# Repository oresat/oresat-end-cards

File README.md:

# "End Card" PCBs for OreSat

OreSat cards in the top position (#1) and bottom position (#20) are special because they interface with
both the solar arrays and with the end caps. They also tend to hold deployable antennas.

## Features

- 4 solar panel connectors
- 3 available RF connectors
- Alternative backplane connectors only (since the solar panel connectors take up the main connector spot)

## Connector information

- TBD.

## LICENSE

Copyright Portland State Aerospace Society 2022.

This documentation describes Open Hardware and is licensed under the CERN OHL v2

You may redistribute and modify this documentation under the terms of the CERN OHL v.1.2. [https://ohwr.org/cernohl](https://ohwr.org/cernohl). This documentation is distributed WITHOUT ANY EXPRESS OR IMPLIED WARRANTY, INCLUDING OF MERCHANTABILITY, SATISFACTORY QUALITY AND FITNESS FOR A PARTICULAR PURPOSE. Please see the CERN OHL v2 for applicable conditions.

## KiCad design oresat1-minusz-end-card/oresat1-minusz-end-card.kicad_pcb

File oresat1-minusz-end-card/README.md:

---
title: "**OreSat1 -Z End Card**"
subtitle: |
  **Fabrication and Assembly Information**\
  For build TIME-STAMP
fontsize: 10pt
geometry:
  - margin=0.5in
toc: true
toc-depth: 2
colorlinks: true
urlcolor: blue
---

\newpage

# About this Board

## Board Description

The OreSat1 -Z End Card fits in the very "bottom" slot (Slot #20?) in the OreSat1 2U backplane. It's special because it hosts whatever antenna is on the -Z face of the satellite, which in this case is an L band monopole, a UHF band monopole, and an L1 band GPS patch antenna. The -Z End Card:

- Connects to the backplane with a main connector and three RF SMPM connectors
- Connects two -Z solar modules to the backplane (two of the solar module spots are taken up by the copper radiator panels for the CFC assembly)
- Routes an SMPM connector to a U.FL connector to jump up to the -Z End Cap's L1 band GPS patch antenna
- Has an OPD circuit to control:
   - Deploying the monopole antennas
   - Switching C3-UART to any of the -Z solar modules

## Documentation Links

- -Z End Card Git repository: <https://github.com/oresat/oresat-end-cards>
- **TODO:** -Z End Card Design Notes + Design Review Notes

## Documentation Files

| Filename                        | Notes                                    |
| ------------------------------- | ---------------------------------------- |
| README.pdf                      | This README file                         |
| PROJECT-NAME-outline.dxf        | Board outline (with holes) in DXF format |
| PROJECT-NAME-pcba.step          | 3D model of PCBA (with components)       |
| PROJECT-NAME-render-bot.jpg     | Render of the top of the 3D model        |
| PROJECT-NAME-render-bot.jpg     | Render of the bottom of the 3D model     |
| PROJECT-NAME-schematic.pdf      | PDF of board schematics                  |

## Contact Information

- Website: <https://www.oresat.org/>
- Email: <oresat@pdx.edu>
- Instagram: @pdxaerospace

## Board Renders

{width=50%}
{width=50%}

\newpage

# Printed Circuit Board (PCB) Fabrication Information

## Board Info

- 4 layer board
- Bounding box is 99.8 x 94.6 mm (3.93 x 3.72 in)
- Board thickness is 1.59 mm (0.063 inch)
- **Important:** See Materials and Stack Up sections below

## Board Requirements

- Design Rules
    - Minimum Trace / Space design rules
       - Outer layers: 0.127 mm (5.0 mil) / 0.127 mm (5.0 mil)
       - Inner layers: 0.127 mm (5.0 mil) / 0.127 mm (5.0 mil)
    - Outer dimension router tolerance: +/- 0.254 mm (10.0 mil)
    - Hole placement tolerance: +/- 0.075 mm (3.0 mil)
    - Inner tab routed slot tolerance: +/- 0.254 mm (10.0 mil)
- Drills
   - Drill Positional Tolerance: 0.051 mm (2.0 mil)
   - Drill Size tolerance: +/- 0.064 mm (2.5 mil)
- Plated/Un-plated holes
  - There are 16 un-plated (NPT) holes
  - There are 434 plated through (PTH) holes
  - PTH minimum diameter: 0.254 mm (10 mil)
  - PTH minimum annulus: 0.102 mm (4 mil) radius
- Outline/Routing
  - Requires a 1.0 mm or smaller diameter routing bit
- Slots
  - There are two 1.0 mm plated slots.
- Cutouts
  - There is are two cutouts.
- There are 3 fiducials on the top layer and 3 fiducials on the bottom layer.
- Panel tabs ("mouse bites")
   - Card edges must be smooth; no mouse bites or other intrusions into the card outline.
   - If external mouse bites are required, minimize and customer will remove by hand before assembly.
- If not otherwise specified, build to IPC 6012 Class 2 or better.

## Materials

- Controlled impedance
   - The stackup is critical for the performance of high speed signals on this board.
   - As long as the stackup is controlled, the board is not considered controlled impedance.
- Isola FR408HR or material with equivalent Dk.
- Board Surface treatment should be ENIG, althogh immersion Silver is acceptable.
- White silkscreen on top and bottom surface
- Taiyo PSR-4000 or equivalent soldermask on top and bottom, no requirements for color.

## Stack Up

| Layer         | Thickness           | Notes                                        |
|---------------|---------------------|----------------------------------------------|
| Top Copper    | 0.043 mm /  1.7 mil |  Layer 1 foil, 1 oz Cu after plating         |
| prepreg       | 0.200 mm /  7.9 mil |  Prepreg - Isola FR408HR 2113                |
| Layer 2       | 0.018 mm /  0.7 mil |  Layer 2 foil, 0.5 oz Cu                     |
| Core          | 0.991 mm /   39 mil |  Core Isola FR408HR                          |
| Layer 3       | 0.018 mm /  0.7 mil |  Layer 3 foil, 0.5 oz Cu                     |
| prepreg       | 0.200 mm /  7.9 mil |  Prepreg - Isola FR408HR 2113                |
| Bottom Copper | 0.043 mm /  1.7 mil |  Layer 4 foil, 1 oz copper after plating     |
| **Total Stackup** | **1.588 mm / 62.5 mil** |                                      |

## Array / Panel Information

- Coordinate with Contract Manufacturer (CM) for optimal size of this panel.
- If no feedback from CM, then produce single boards (no panel).

## Fabrication Files

### IPC-2581 File

| Filename                 | Notes                                   |
| ------------------------ | --------------------------------------- |
| PROJECT-NAME-ipc2581.xml | IPC-2581 board information file         |

### Legacy PCB Files

| Filename                      | Notes                                         |
| ------------------------------| --------------------------------------------- |
| PROJECT-NAME-Edge_Cuts.gbr    | RS274X file for the dimension (outline) layer |
| PROJECT-NAME-F_Silkscreen.gbr | RS274X file for the top silkscreen            |
| PROJECT-NAME-F_Mask.gbr       | RS274X file for the top soldermask            |
| PROJECT-NAME-F_Cu.gbr         | RS274X file for the top copper layer          |
| PROJECT-NAME-In1_Cu.gbr       | RS274X file for the layer 2 copper            |
| PROJECT-NAME-In2_Cu.gbr       | RS274X file for the layer 3 copper            |
| PROJECT-NAME-B_Cu.gbr         | RS274X file for the bottom copper layer       |
| PROJECT-NAME-B_Mask.gbr       | RS274X file for the bottom soldermask         |
| PROJECT-NAME-B_Silkscreen.gbr | RS274X file for the bottom silkscreen         |
| PROJECT-NAME-NPTH.drl         | Excellon file for non-plated through holes    |
| PROJECT-NAME-PTH.drl          | Excellon file for plated through holes        | 

\newpage

# Printed Circuit Board Assembly (PCBA) Information

## Assembly Info

- Components are on the top and bottom side of the board.
- This PCBA is mostly surface mount (SMT) with a few (THT) components.

## Assembly Requirements

- Assemble to IPC Class 2 or better
- Bake components that are not moisture sealed to appropriate levels as required.
- Solder paste MUST be leaded.
- Aqueous flux and wash strongly preferred.
   - Clean to NASA Standard "Visibly Clean (VC)": No particles or residues are visible to the naked eye.
- No conformal coating.
- Ship in antistatic protective bag

## Component Specific Assembly Information

- SMPM connectors (CM1 - CM3) should be hand-addedaccording to SOP (there is no solder paste for their footprints).
- Monopole antennas must be hand added according to the Antenna SOP.
- Resistor R1 must be hand added according to the OreSat End Card Deployment Resistor Mounting SOP.
- Press fit nuts HW1 - HW6 may be *carefully* added after SMT assembly is completed.

## Assembly Files

### IPC-2581 File

| Filename                 | Notes                           |
| ------------------------ | ------------------------------- |
| PROJECT-NAME-ipc2581.xml | IPC-2581 board information file |

### Bill of Materials (BOM)

| Filename             | Description                            |
| -------------------- | -------------------------------------- |
| PROJECT-NAME-bom.csv | BOM in Comma Separated Variable format |

### Solder Paste Stencils

| Filename                 | Notes                                            |
| ------------------------ | ------------------------------------------------ |
| PROJECT-NAME-B_Paste.gbr | RS274X file for top/front solder paste stencil   |
| PROJECT-NAME-F_Paste.gbr | RS274X file for bottom/back solder paste stencil |

### Mounting/Placement Location

| Filename            | Description                                 |
| ------------------- | ------------------------------------------- |
| PROJECT-NAME-3u.pos | Pick and place locations for components     |

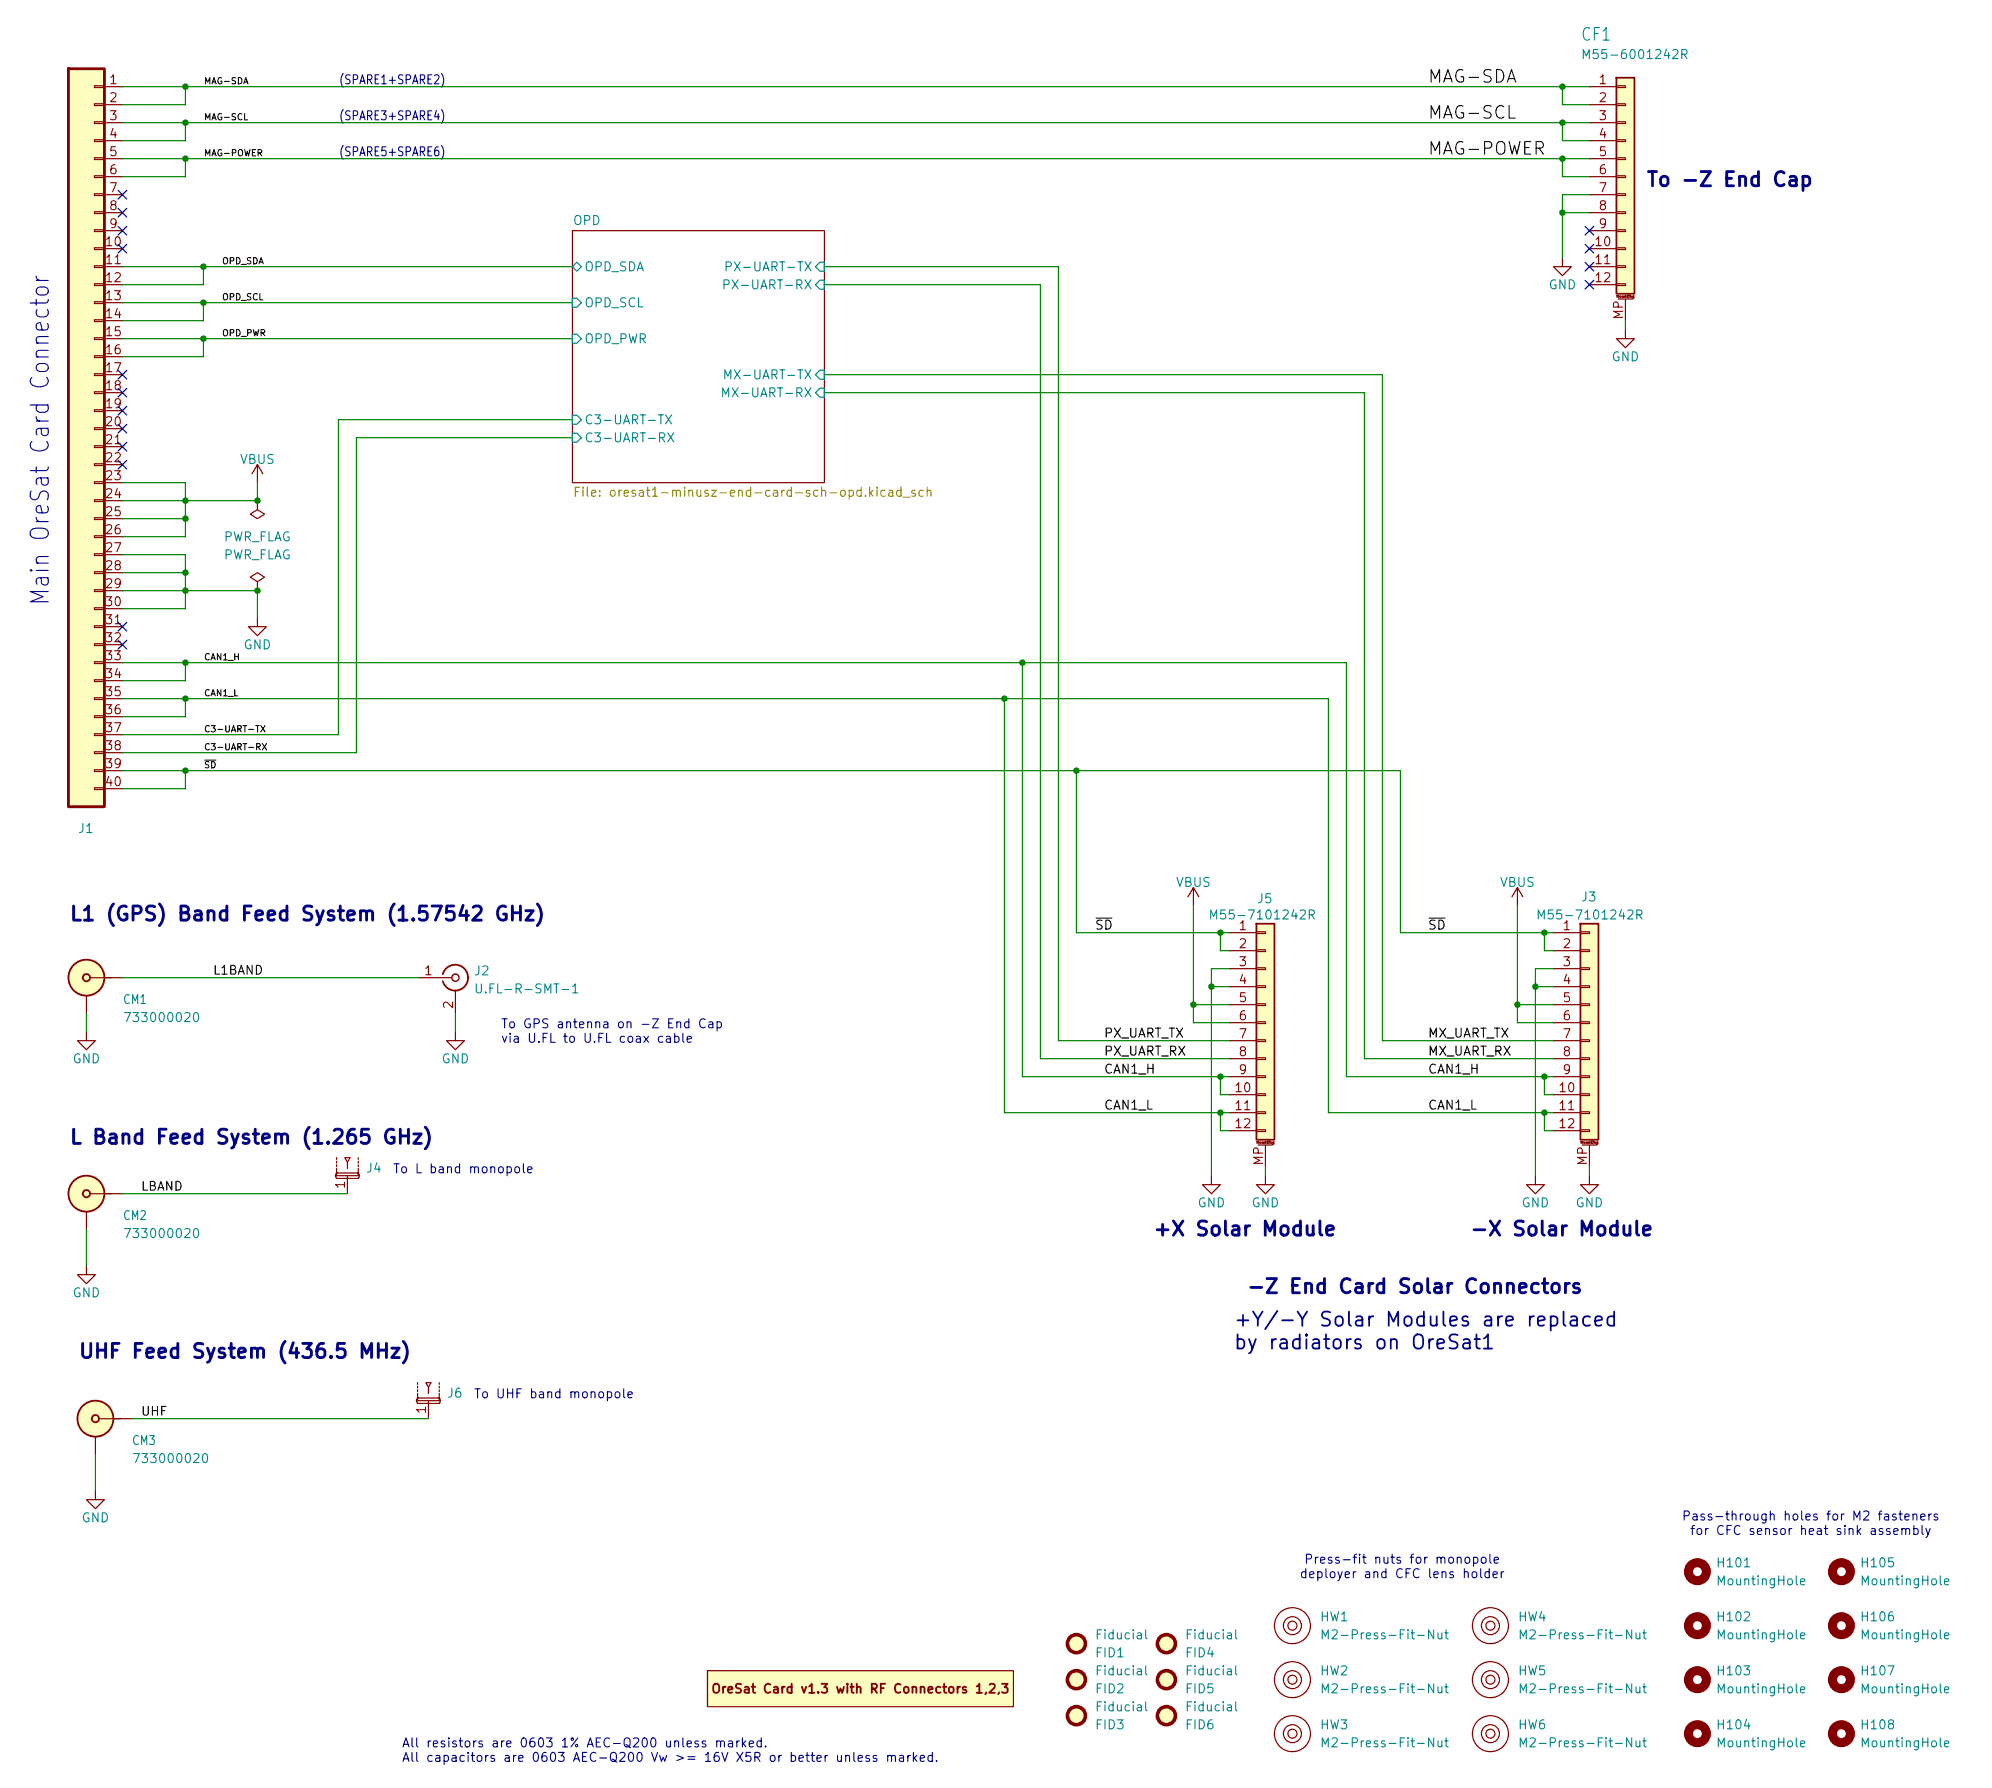
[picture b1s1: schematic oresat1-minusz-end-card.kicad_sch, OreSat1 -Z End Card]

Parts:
CF1: M55-6001242R; J-Harwin-M55-60X1242R; MPN M55-6001242R
CM1, CM2, CM3: 733000020; J-MOLEX-SMPM-073300-002X; MPN 2477330-1
FID1, FID2, FID3, FID4, FID5, FID6: Fiducial; Fiducial_1mm_Mask2mm
H101, H102, H103, H104, H105, H106, H107, H108: MountingHole; MountingHole_5mm
HW1, HW2, HW3, HW4, HW5, HW6: M2-Press-Fit-Nut; MPN N/A
J1: J-SAMTEC-TFM-120-01-L-D-RA; J-SAMTEC-TFM-120-X1-XXX-D-RA; MPN TFM-120-01-L-D-RA
J2: U.FL-R-SMT-1; U.FL_Hirose_U.FL-R-SMT-1_Vertical; MPN U.FL-R-SMT-1(10)
J3, J5: M55-7101242R; J-Harwin-M55-7101242R; MPN M55-7101242R
J4, J6: tape-measure-slot-antenna
PCB1: ORESAT-CARD-V1.3-GENERIC-3RF; ORESAT-CARD-V1.3-3RF

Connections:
/C3-UART-RX: J1.38; also elsewhere on the board
/C3-UART-TX: J1.37; also elsewhere on the board
/CAN1_H: J1.33, J1.34, J3.9, J3.10, J5.9, J5.10
/CAN1_L: J1.35, J1.36, J3.11, J3.12, J5.11, J5.12
/L1BAND: CM1.1 (SIG), J2.1 (In)
/LBAND: CM2.1 (SIG), J4.1
/MAG-POWER: CF1.5, CF1.6, J1.5, J1.6
/MAG-SCL: CF1.3, CF1.4, J1.3, J1.4
/MAG-SDA: CF1.1, CF1.2, J1.1, J1.2
/MX_UART_RX: J3.8; also elsewhere on the board
/MX_UART_TX: J3.7; also elsewhere on the board
/OPD_PWR: J1.15, J1.16; also elsewhere on the board
/OPD_SCL: J1.13, J1.14; also elsewhere on the board
/OPD_SDA: J1.11, J1.12; also elsewhere on the board
/PX_UART_RX: J5.8; also elsewhere on the board
/PX_UART_TX: J5.7; also elsewhere on the board
/UHF: CM3.1 (SIG), J6.1
/~SD: J1.39, J1.40, J3.1, J3.2, J5.1, J5.2
GND: CF1.7, CF1.8, CF1.MP (MountPin), CM1.2 (SHLD), CM2.2 (SHLD), CM3.2 (SHLD), J1.27, J1.28, J1.29, J1.30, J2.2 (Ext), J3.3, J3.4, J3.MP (MountPin), J5.3, J5.4, J5.MP (MountPin); also elsewhere on the board
VBUS: J1.23, J1.24, J1.25, J1.26, J3.5, J3.6, J5.5, J5.6; also elsewhere on the board

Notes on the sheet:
(SPARE5+SPARE6)
(SPARE3+SPARE4)
-Z End Card Solar Connectors
Pass-through holes for M2 fasteners for CFC sensor heat sink assembly
To L band monopole
+Y/-Y Solar Modules are replaced by radiators on OreSat1
All resistors are 0603 1% AEC-Q200 unless marked. All capacitors are 0603 AEC-Q200 Vw >= 16V X5R or better unless marked.
+X Solar Module
Main OreSat Card Connector
Press-fit nuts for monopole deployer and CFC lens holder
To UHF band monopole
(SPARE1+SPARE2)
UHF Feed System (436.5 MHz)
L1 (GPS) Band Feed System (1.57542 GHz)
To -Z End Cap
To GPS antenna on -Z End Cap via U.FL to U.FL coax cable
L Band Feed System (1.265 GHz)
-X Solar Module

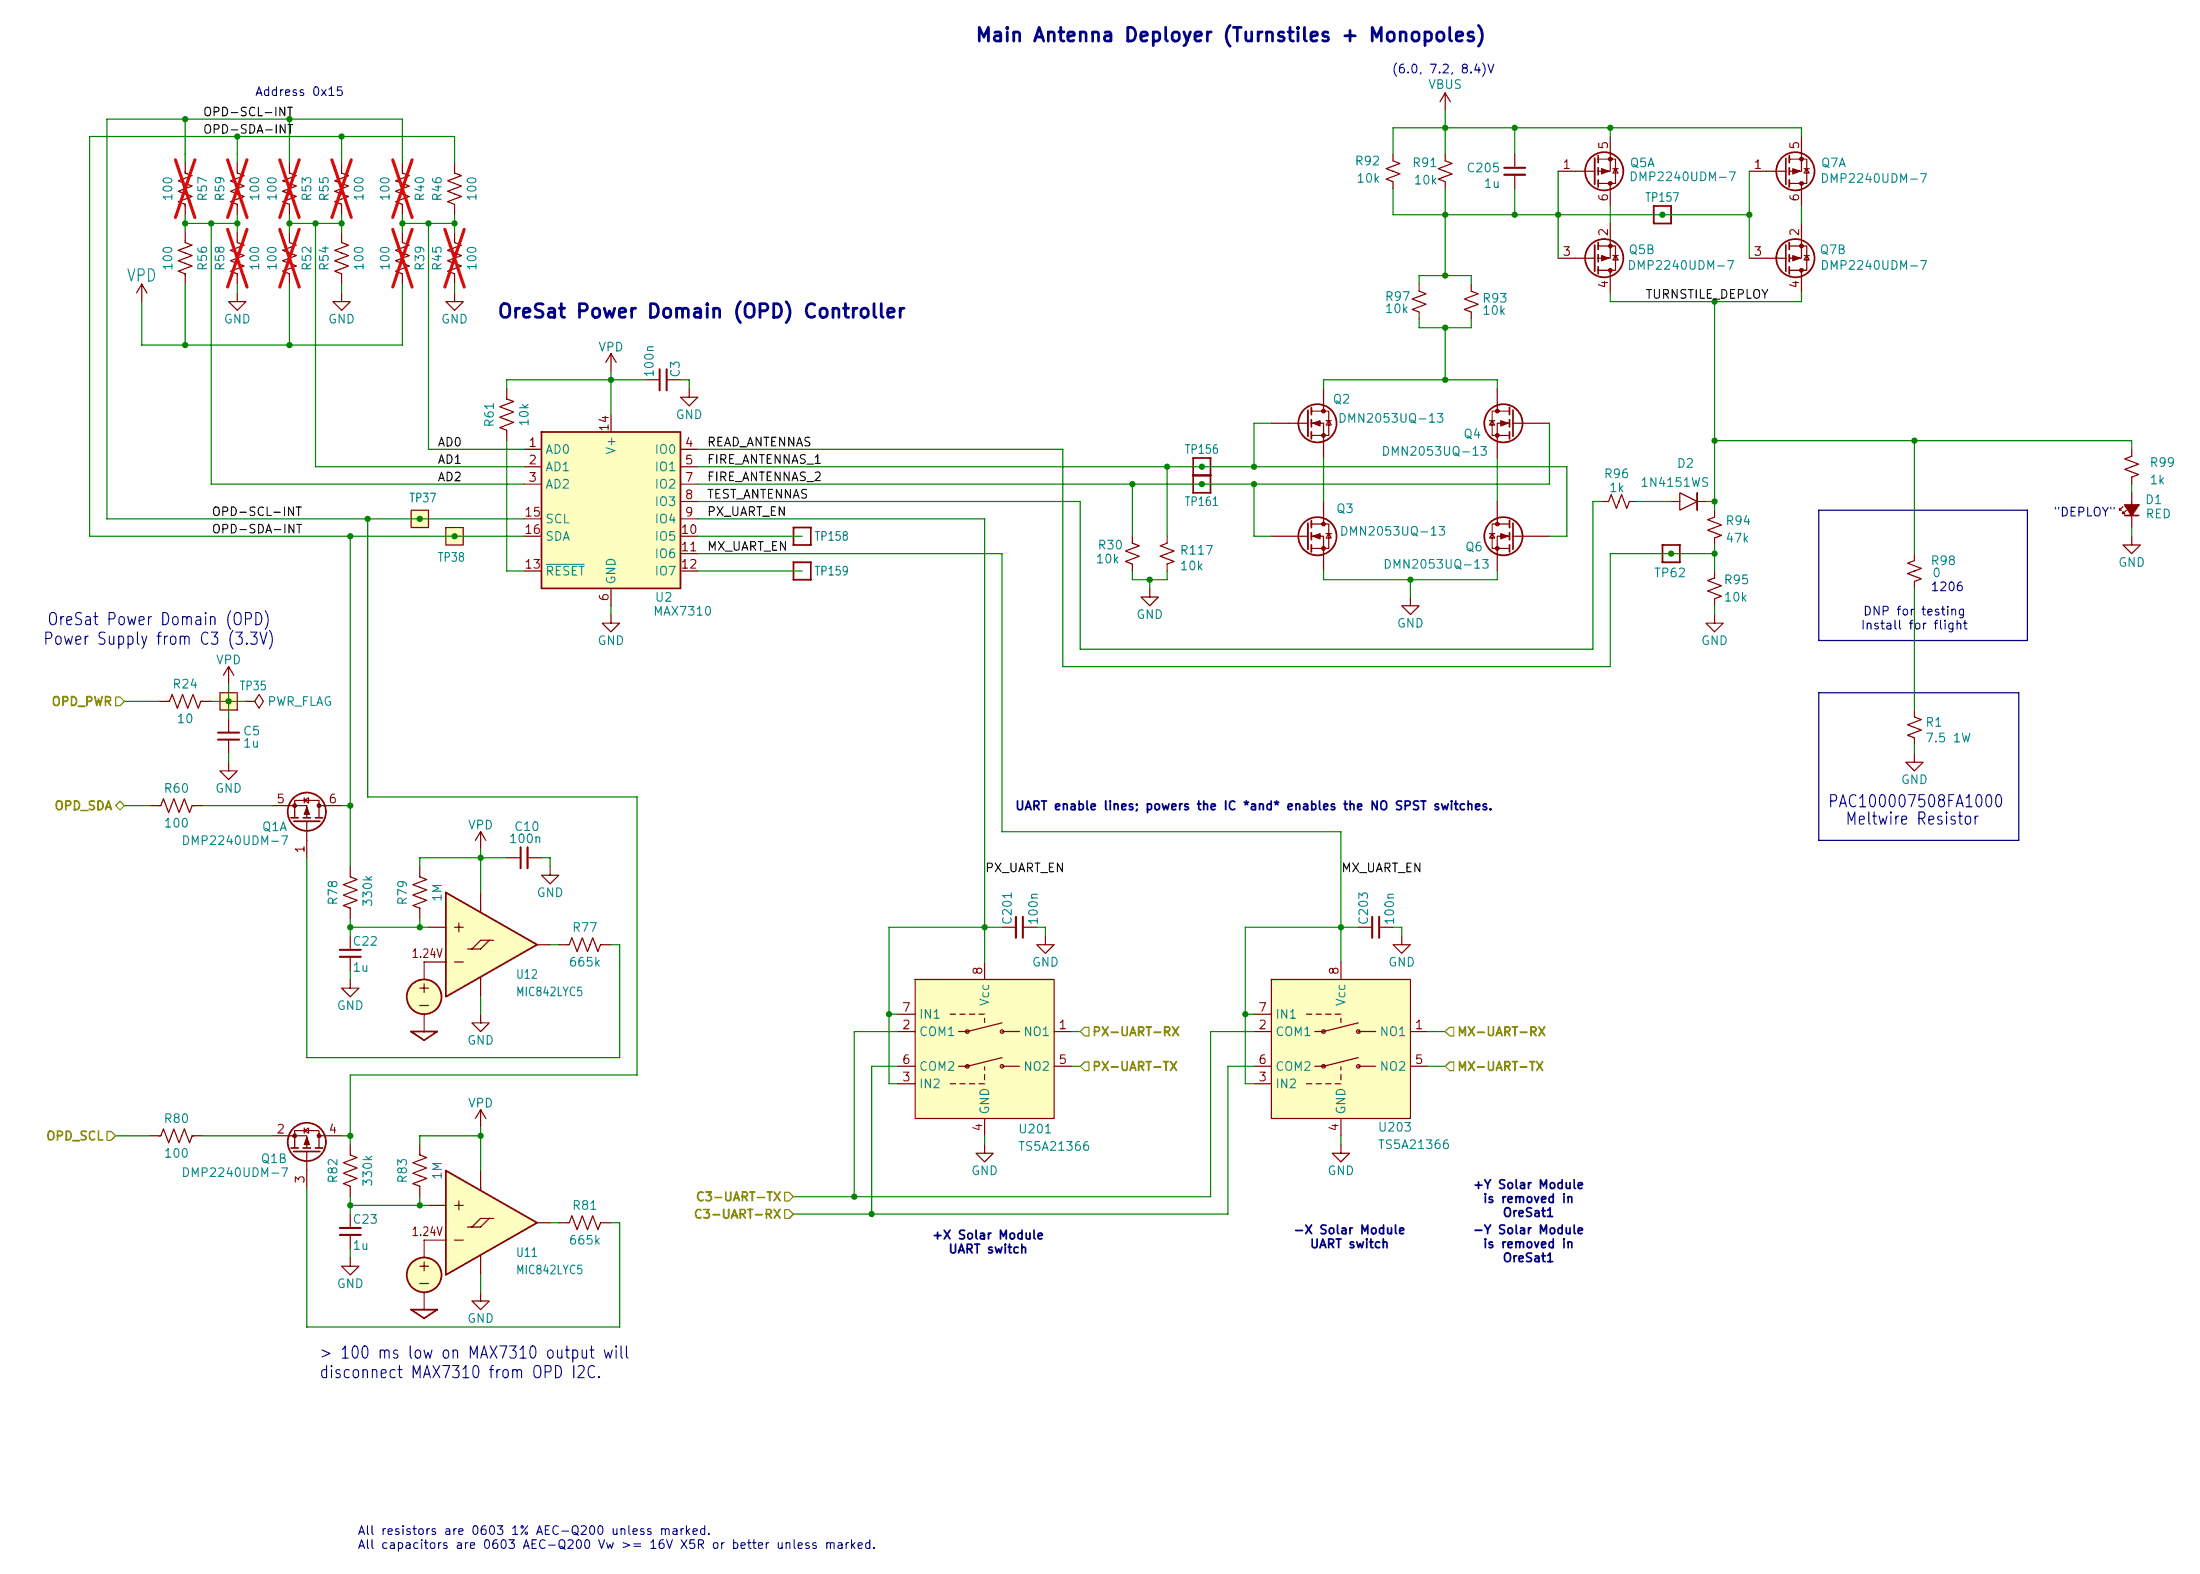
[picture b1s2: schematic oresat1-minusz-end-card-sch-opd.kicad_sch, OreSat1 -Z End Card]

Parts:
C3, C10, C201, C203: 100n; 0603-C-NOSILK; MPN C0603C104K5RACAUTO
C5, C22, C23, C205: 1u; 0603-C-NOSILK; MPN GRT188R71E105KE13D
D1: RED; LED_0603_1608Metric; MPN 150060RS75000
D2: 1N4151WS; D_SOD-323; MPN 1N4151WS-E3-08
Q1, Q5, Q7: DMP2240UDM-7; SOT-23-6; MPN DMP2240UDM-7
Q2, Q3, Q4, Q6: DMN2053UQ-13; SOT-23-3; MPN DMN2053UQ-13
R1: 7.5 1W; R-PAC100-FOR-MELTWIRE; MPN PAC100007508FA1000
R24: 10; 0603-C-NOSILK; MPN RMCF0603FT10R0
R30, R61, R91, R92, R93, R95, R97, R117: 10k; 0603-C-NOSILK; MPN RMCF0603FT10K0
R39, R40, R45, R52, R53, R55, R57, R58, R59: 100; 0603-C-NOSILK; MPN RMCF0603FT1K00; not fitted
R46, R54, R56, R60, R80: 100; 0603-C-NOSILK; MPN RMCF0603FT100R
R77, R81: 665k; 0603-C-NOSILK; MPN RMCF0603FT665K
R78, R82: 330k; 0603-C-NOSILK; MPN RMCF0603FT330K
R79, R83: 1M; 0603-C-NOSILK; MPN RMCF0603FT1M00
R94: 47k; 0603-C-NOSILK; MPN RMCF0603FT47K0
R96, R99: 1k; 0603-C-NOSILK; MPN RMCF0603FT1K00
R98: 0; 1206-C; MPN RMCF1206ZG0R00
TP35, TP37, TP38: Test-Point; TestPoint-0.75mm-th
TP62, TP156, TP157, TP158, TP159, TP161: Test-Point; TestPoint_Pad_D1.0mm
U2: MAX7310; QFN-16-1EP_4x4mm_P0.65mm_EP2.1x2.1mm; MPN MAX7310ATE+
U11, U12: MIC842LYC5; SOT-353_SC-70-5; MPN MIC842LYC5-TR
U201, U203: TS5A21366; VSSOP-8_2.3x2mm_P0.5mm; MPN TS5A21366DCUR

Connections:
/C3-UART-RX: U201.6 (COM2), U203.6 (COM2); also elsewhere on the board
/C3-UART-TX: U201.2 (COM1), U203.2 (COM1); also elsewhere on the board
/MX_UART_RX: U203.1 (NO1); also elsewhere on the board
/MX_UART_TX: U203.5 (NO2); also elsewhere on the board
/OPD/AD0: R39.1, R40.2, R45.2, R46.1, U2.1 (AD0)
/OPD/AD1: R52.1, R53.2, R54.2, R55.1, U2.2 (AD1)
/OPD/AD2: R56.1, R57.2, R58.2, R59.1, U2.3 (AD2)
/OPD/FIRE_ANTENNAS_1: Q2.1 (G), Q6.1 (G), R117.1, TP156.1 (1_1), U2.5 (IO1)
/OPD/FIRE_ANTENNAS_2: Q3.1 (G), Q4.1 (G), R30.1, TP161.1 (1_1), U2.7 (IO2)
/OPD/MX_UART_EN: C203.1, U2.11 (IO6), U203.3 (IN2), U203.7 (IN1), U203.8 (Vcc)
/OPD/OPD-SCL-INT: Q1.4 (D), R40.1, R53.1, R57.1, R82.2, TP37.1 (1_1), U2.15 (SCL)
/OPD/OPD-SDA-INT: Q1.6 (D), R46.2, R55.2, R59.2, R78.2, TP38.1 (1_1), U2.16 (SDA)
/OPD/PX_UART_EN: C201.1, U2.9 (IO4), U201.3 (IN2), U201.7 (IN1), U201.8 (Vcc)
/OPD/READ_ANTENNAS: R94.2, R95.1, TP62.1 (1_1), U2.4 (IO0)
/OPD/TEST_ANTENNAS: R96.1, U2.8 (IO3)
/OPD/TURNSTILE_DEPLOY: D2.1, Q5.4 (D), Q7.4 (D), R94.1, R98.1, R99.1
/OPD_PWR: R24.1; also elsewhere on the board
/OPD_SCL: R80.1; also elsewhere on the board
/OPD_SDA: R60.1; also elsewhere on the board
/PX_UART_RX: U201.1 (NO1); also elsewhere on the board
/PX_UART_TX: U201.5 (NO2); also elsewhere on the board
GND: C3.1, C5.2, C10.1, C22.2, C23.2, C201.2, C203.2, D1.1 (K), Q3.2 (S), Q6.2 (S), R1.2, R30.2, R45.1, R54.1, R58.1, R95.2, R117.2, U2.6 (GND), U2.17 (GND), U11.2 (GND), U12.2 (GND), U201.4 (GND), U203.4 (GND); also elsewhere on the board
unnamed: D1.2 (A), R99.2
unnamed: D2.2, R96.2
unnamed: Q1.1 (G), R77.2
unnamed: Q1.5 (S), R60.2
unnamed: Q1.3 (G), R81.2
unnamed: Q1.2 (S), R80.2
unnamed: Q2.3 (D), Q4.3 (D), R93.1, R97.1
unnamed: Q2.2 (S), Q3.3 (D)
unnamed: Q4.2 (S), Q6.3 (D)
unnamed: Q5.2 (S), Q5.6 (D)
unnamed: C205.1, Q5.1 (G), Q5.3 (G), Q7.1 (G), Q7.3 (G), R91.2, R92.2, R93.2, R97.2, TP157.1 (1_1)
unnamed: Q7.2 (S), Q7.6 (D)
unnamed: R1.1, R98.2
unnamed: TP158.1 (1_1), U2.10 (IO5)
unnamed: TP159.1 (1_1), U2.12 (IO7)
unnamed: R61.1, U2.13 (~RESET)
unnamed: C23.1, R82.1, R83.1, U11.1 (INP)
unnamed: R81.1, U11.4 (OUT)
unnamed: C22.1, R78.1, R79.1, U12.1 (INP)
unnamed: R77.1, U12.4 (OUT)
VBUS: C205.2, Q5.5 (S), Q7.5 (S), R91.1, R92.1; also elsewhere on the board
VPD: C3.2, C5.1, C10.2, R24.2, R39.2, R52.2, R56.2, R61.2, R79.2, R83.2, TP35.1 (1_1), U2.14 (V+), U11.5 (VDD), U12.5 (VDD)

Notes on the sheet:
1206
-Y Solar Module is removed in OreSat1
UART enable lines; powers the IC *and* enables the NO SPST switches.
(6.0, 7.2, 8.4)V
Main Antenna Deployer (Turnstiles + Monopoles)
"DEPLOY"
Meltwire Resistor
+Y Solar Module is removed in OreSat1
-X Solar Module UART switch
DNP for testing Install for flight
OreSat Power Domain (OPD) Power Supply from C3 (3.3V)
All resistors are 0603 1% AEC-Q200 unless marked. All capacitors are 0603 AEC-Q200 Vw >= 16V X5R or better unless marked.
OreSat Power Domain (OPD) Controller
> 100 ms low on MAX7310 output will disconnect MAX7310 from OPD I2C.
Address 0x15
+X Solar Module UART switch
PAC100007508FA1000

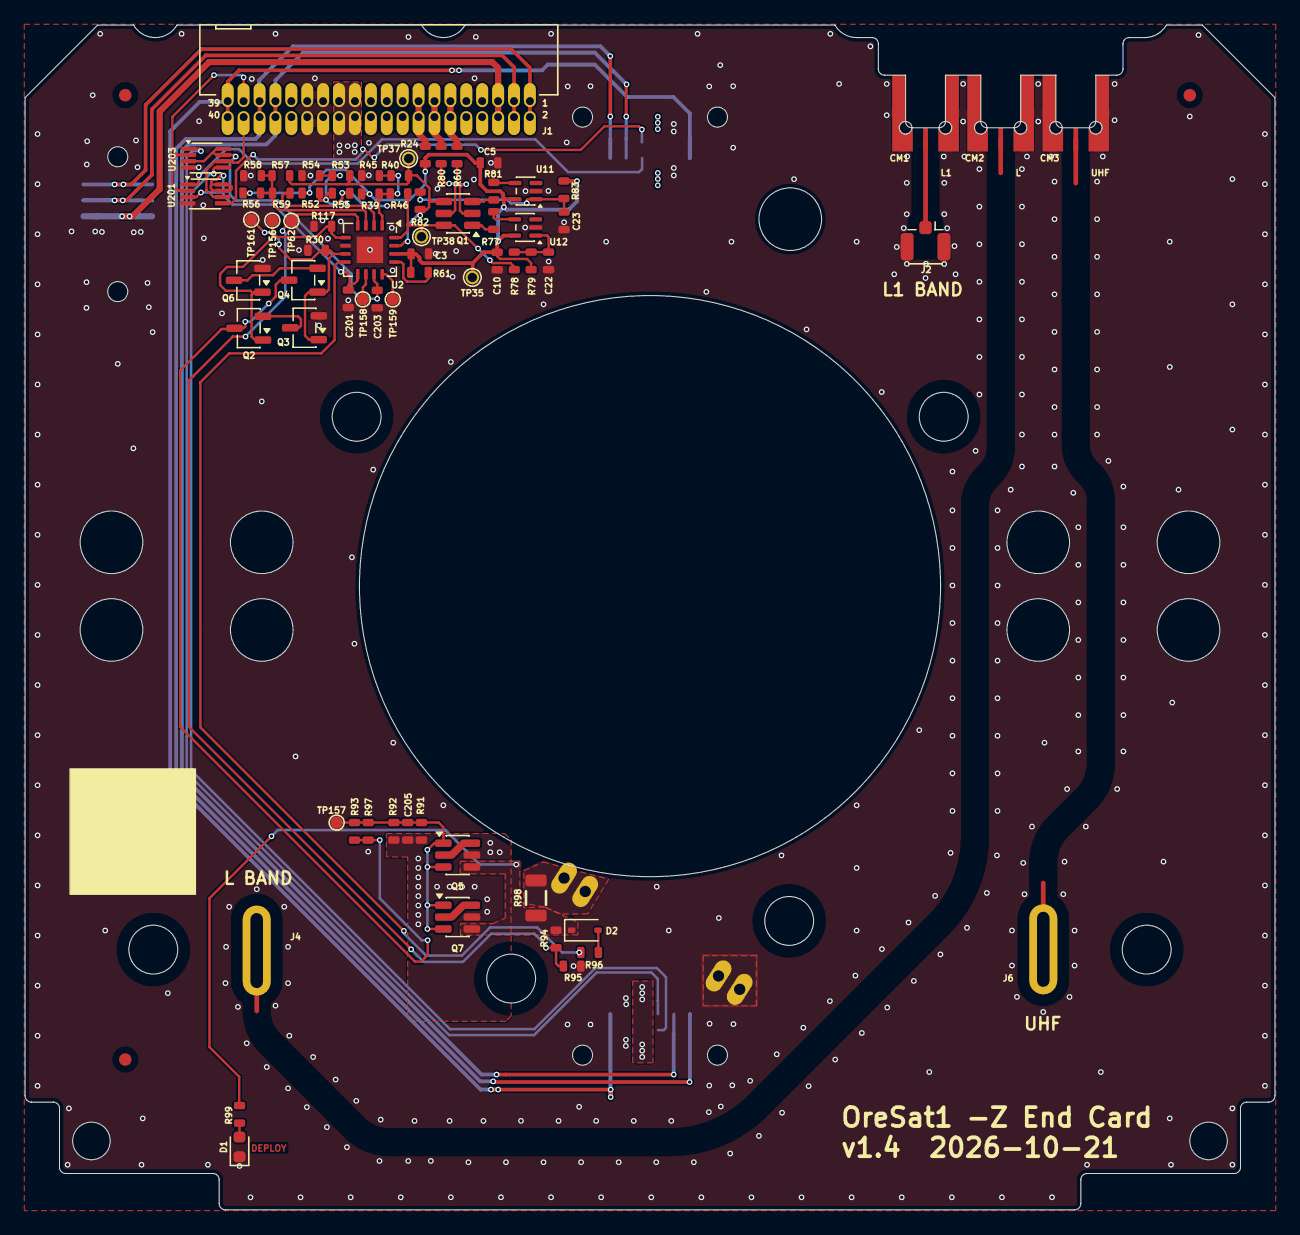
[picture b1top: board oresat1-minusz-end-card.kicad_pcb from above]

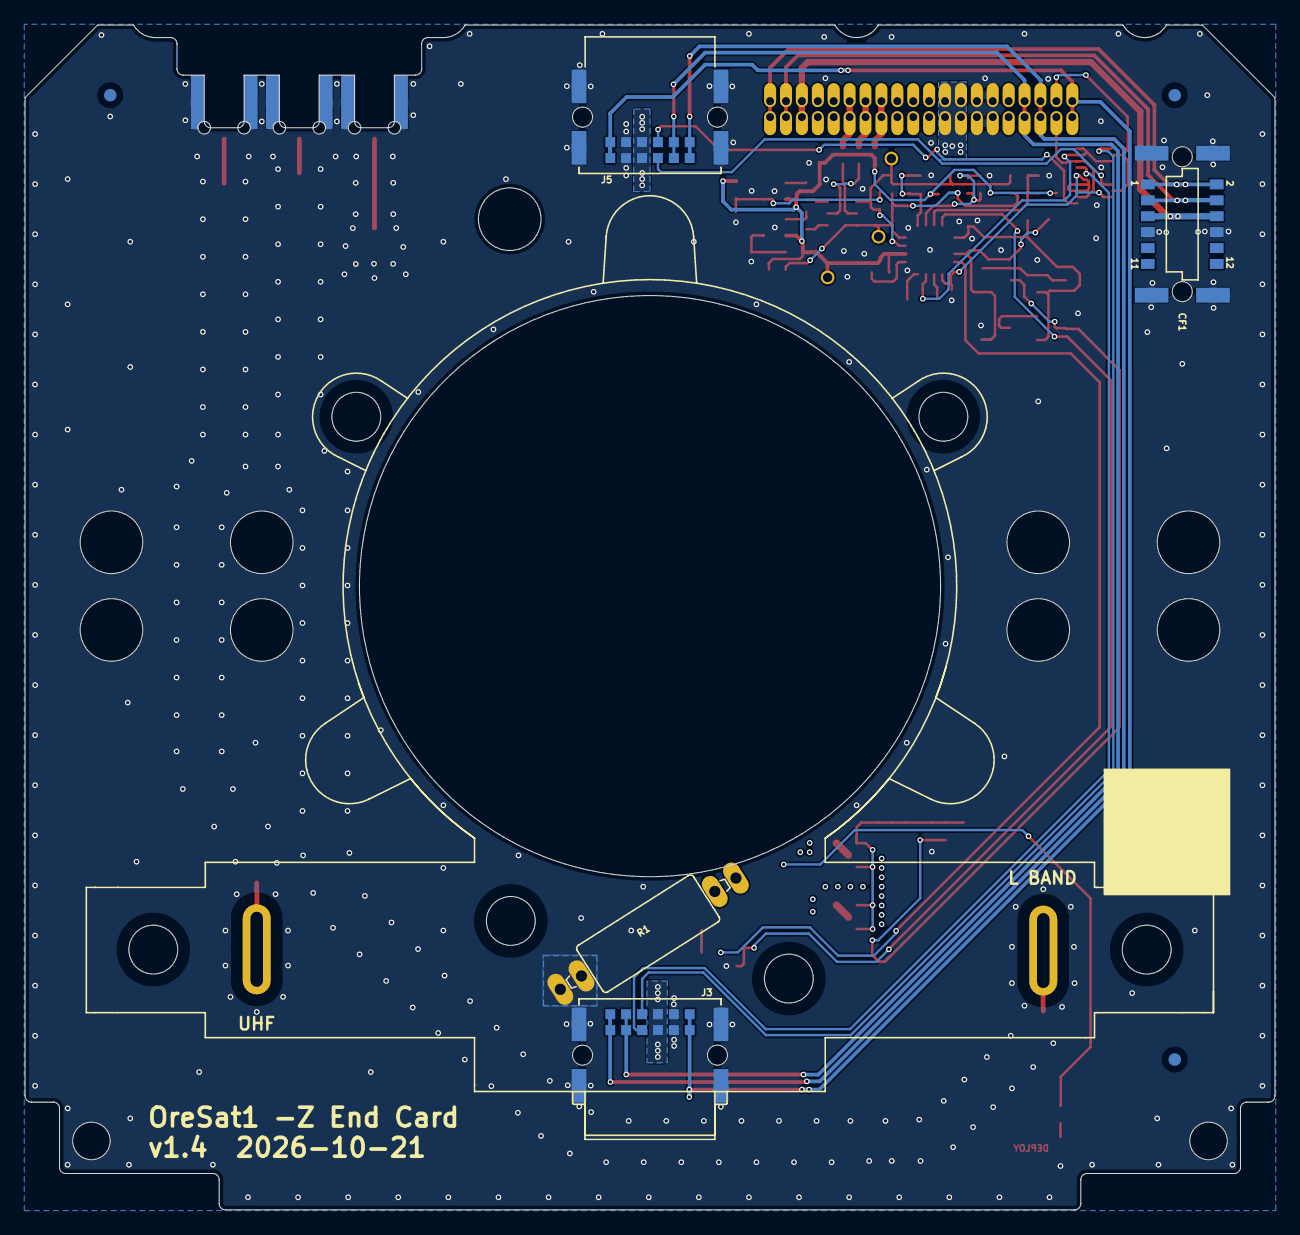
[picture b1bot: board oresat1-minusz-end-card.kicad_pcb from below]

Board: 4 copper layers, 99.8 x 94.6 mm, 96 parts (13 on the bottom side), 53 nets.

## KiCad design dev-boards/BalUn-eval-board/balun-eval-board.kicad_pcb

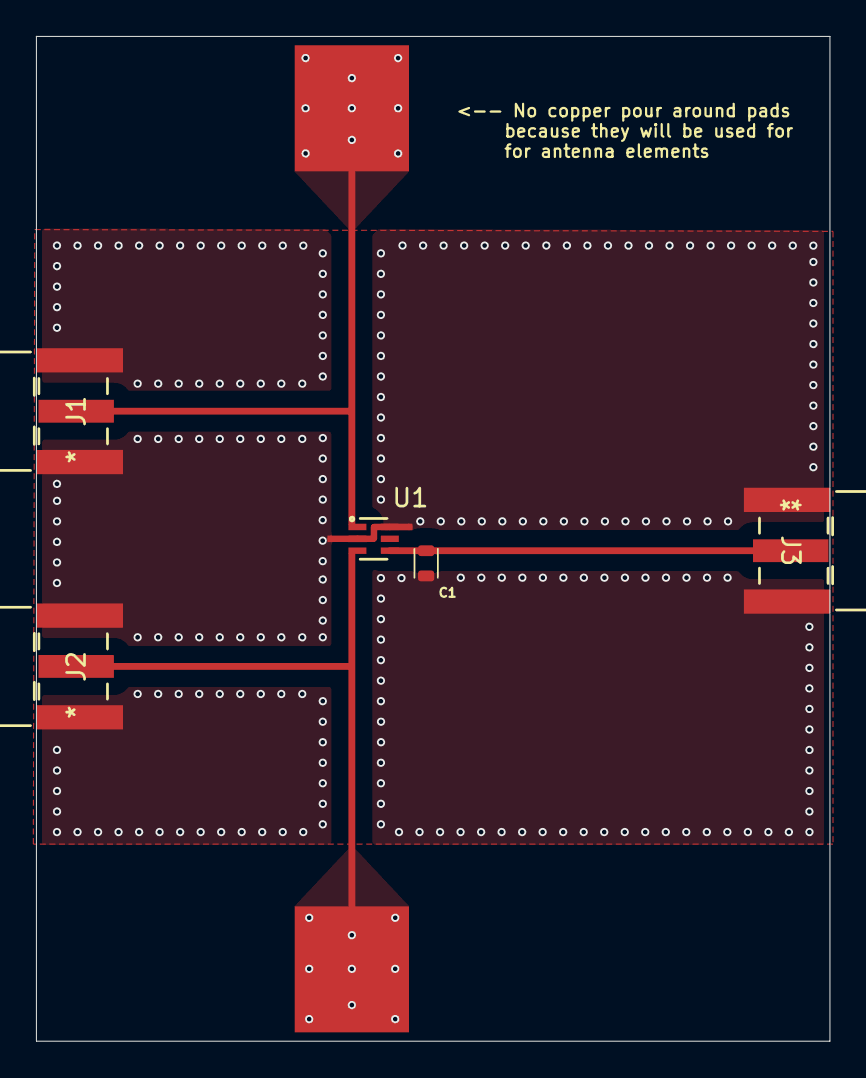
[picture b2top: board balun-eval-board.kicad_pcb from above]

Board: 4 copper layers, 44.1 x 55.8 mm, 7 parts (0 on the bottom side), 4 nets.

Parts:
C1: C; 0603-C
J1, J2, J3: SMA-142-0711-201; SMA-J-P-H-ST-EM1
TP1, TP2: TestPoint_Pad_D1.0mm
U1: NCS2-62+; 2450FB15A050E_JOT

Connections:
GND: C1.1, J1.2 (In), J1.3 (Ext), J2.2 (In), J2.3 (Ext), J3.2 (In), J3.3 (Ext), U1.2 (GND), U1.6 (GND)
unnamed: C1.2, J3.1, U1.4
unnamed: J1.1, TP1.1 (1_1), U1.1
unnamed: J2.1, TP2.1 (1_1), U1.3

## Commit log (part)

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2018-12-16 Outline of boards, license file, readme.
2018-12-17 Created library and placed solar connectors based on structure updates from yesterday.
2018-12-19 Worked with Joe to check connectors, preliminary layout, 2 layers for now.
2018-12-21 Updated +Z end card, with end cap attachment to magnetometers.
2018-12-22 +Z end cards ready for mfg, as far as we know!
2019-02-26 Added debug board that comes off of the +Z and -Z end cards (past the caps).
2019-02-26 Updated end cards with antenna keep outs, and rewired +Z end card debug port and started on +Z schematic update with power domain.
2019-02-27 Added OreSat power domain -- via design blocksgit status -- and OMG it's doneish.
2020-11-23 Moved OreSat0 +Z end card and mezzanine to the end card directory, where it really ought to have been. Updated the card and mezanine with Card outline v1.3, and added a first pass of the S band feed 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
2020-11-24 Final cleanup and polish of v1.1 OreSat0 +Z end card and mezzanine. Fixed S band 1/4 wave, lots of stiching and polish, fixed radial TCREAM on the contact pads, lots of TNAMES polish.
2020-11-24 Clean up BOM and part numbers. Ready for v1.1 fab.
2020-11-24 Switched to a QCN-27D+ (with DC passthrough) for S band, and made the U and L band 1/4 wave lengths a bit more precise after getting precise lengths from Eric.
2020-12-08 Small tweaks; reduced mezanine board size. Added flight tags. Off to fab!
2021-01-04 Forgot to remove a meltwire resistor.
2021-04-08 Version 1.2 of the OreSat0 end card and mezzanine.
    Largest change is the position of the antennas on the end card; changes to the deployer changed the antenna placement which triggered everything else.
    Other changes include fiducials, attributes cleanup, move to 0603 resistors, and misc polish.
2021-04-21 Fixed bad part number for end card to end cap connector.
2021-10-03 replaced S-band net labels with L1-band labels, swapped the S-band hybrids with L-band hybrids, recalculated 1/4 wavelength trace length, routed a new short+1/4 wavelength trace
2021-10-10 added vias along new short+1/4wave trace
2021-10-10 added bstop new short+1/4wave trace
2021-10-10 adjusted the length of L1BAND_0 and L1BAND_90 to match L1BAND_180 and L1BAND_270
2021-10-10 adjusted bstop for L1BAND_0 AND L1BAND_90
2021-11-04 v2.0 card, mezzanine, and BOM for v2.0. Moved UHF hybrids to avoid melt wire resistor leads. Updated BOM to reflect new v2.0 design.
2021-11-04 Added in-stock quantities
2022-07-27 Moved -z to KiCad and labeled RF connectors
2022-07-27 Move OreSat0 +Z end card to its own directory; removed amazingly old end cards that aren't relevant anymore.
2022-07-27 Fixed some errors on the ancient -z end card
2022-07-27 Removed the ancient -z end card
2022-07-27 renamed OreSat0 +Z end card to a more descriptive, non-mission name
2022-07-27 Updated liscense to V2
2022-07-27 Moved +z with turnstile to KiCad
2022-07-27 Added generic +z end card
2023-02-12 Renamed folders to satellite names as per other repos
2023-02-19 Added generic minusZ end card
2023-02-19 Added generic variant of the OreSat0.5 -Z end card
2023-02-19 Added new outline
2023-02-19 Added new outine
2023-02-19 First rev of OreSat0.5 +Z end card. Updated helical deployer, removed as much EAGLE cruft as easily possible, killed multiple sch sheets.
2023-02-20 More KiCADing, new fiducials and footprints, fixed ERC and DRC. Now waiting on Cesar to do stuff.
2023-02-20 Updated filename for OreSat0.5 +Z end card
2023-02-20 Updated +Z end card connector symbols
2023-02-20 Fixed +Z end card backplane connector library warning
2023-02-20 Updated -Z end card and replaced eagle imported libraries with kicad libraries
2023-02-20 -Z end card design review changes, and added antenna feeds
2023-02-21 Added helical landing pad and left hopefully enough room for Garrett to put in matching components.
2023-02-21 Rounded out RF trace corners on -Z end card
2023-02-21 added Matching Components
    Added matching components for s band antenna, ground stitching
2023-02-21 Updated CAM settings on PCB.
2023-02-21 OMG what happened to the names of this card? Fixing.
2023-02-21 fix silkscreen for -z end card
2023-02-21 Updated readme, moved generic to not oresat0.5
2023-02-21 removing build files, how did these even get added?
2023-02-21 CAM file changes for end card PCBs.
2023-07-17 Updated OreSat 0.5 end card board outlines and mounting holes, and fixed KiCad library warnings
2023-07-28 Updated -Z end card and DXF
2023-07-28 Updated -Z end card date/version number on silkscreen
2023-09-03 Updated -Z end card
2023-09-03 Updated +Z end card
2023-09-11 Updated mounting hole on +Z end card
2023-09-15 Fixed up OreSat0.5 -Z end card: Added hole for U.FL connector to get to GPS antnena, fixed library paths which seemed broken, replaced older EAGLE files too, fixed schematic/board disconnect with ref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
2023-09-15 Oresat0.5 +Z end card: v1.1. Updated to latest KiCAD.
2023-09-15 Fixed mispelling in name
2023-12-15 Moves antenna connection from large vias to slots so we don't need an a lead on the 1/4 inch tape measure antennas.
2024-02-26 Added latest DXF of card outline.
2024-02-26 Updated +Z end card mounting holes
2024-02-26 Added RF strip across hole to keep out ground plane.
2024-03-22 Updated solar module connector positions
2024-03-24 Added updated detailed DXF for +Z end card
2024-04-01 Updated date and unecessary polish on planes, including fillets and just more planes with more vias.
2024-04-01 Updated date, and unecessary and obsessive widening and smoothing of planes.
2024-04-28 Updated helical matching network components and values
2024-05-06 Added M2 fastener holes back into the -Z end card. Rev'd to v1.4.
2024-08-19 initial mounting holes changes for new deployer
2024-08-20 Revert "initial mounting holes changes for new deployer" -- oops, wrong end card.
    This reverts commit 281d3ddd2ce643add95357c75bebd497bf0c76a9.
2024-08-20 Updated hole positions for single door deployer. TODO: fix weird net class errors that shouldn't exist.
2024-09-10 changed resistor placement
2024-09-11 fixed silkscreen, fixed resistor helical deployer zone
2024-09-19 added components in symbol field for BOM
2024-09-20 Final polish for v1.4. Added more stiching vias, cleaned up some DRCs that were stupid, added more layers to deployment resistor pads, now sending off to Osh Park.
2024-11-03 R2 and J6 excluded from BOM and set as DNP
2025-09-23 Moved Mezz Eagle Files to Their Own Folder
2025-09-23 Imported Mezz Files to KiCAD
2025-09-23 Fixed Spelling Mistake
2025-09-23 Fixed Board Outline
2026-01-11 Creating OreSat1 end card folder for Spencer to start adding OPD deployer circuitry. Also probably needs updates for +Z end card for new helical deployer.
2026-02-01 add OPD and deployer circuitry
2026-02-01 add OPD and deployer circuitry, some fixes needed
2026-02-10 v1.1
2026-02-17 v1.2
2026-02-18 v1.1, theoretically done
2026-02-19 v1.3, theoretically done
2026-02-24 OreSat1 -Z end card update
    Upgraded symbols, fixed BOM and added presets, and added UART switches for new solar modules. Clleaned up layout, including some planes and footprints. Still more left to do, but it's more ready to g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
2026-02-26 Rerouted -Z endcard & created new file for ESI dipole v1
2026-02-26 moved esi file out of oresat
2026-02-27 Changed symbols & fab layout
2026-02-27 Design review, more to do!
2026-03-01 Dipole schematic: added balun & footprints. Pre-tracing
2026-03-02 Started RF tracing, not complete -- maybe need to move the balun b/c microstrip turns are too sharp
2026-03-05 renamed ESI -Z end card to combat Shae's weird naming conventions
2026-03-06 Finalized dipole changes, added -/+ Y solar mods. Believe this is finished
2026-03-08 shifted and softened microstrip curves
2026-03-09 bom finished
2026-03-09 Fixed schematic label issues and routed solar uarts
2026-03-09 fixed shcematic issues and routing, updated footprints
2026-03-09 mounting hole parity fix (internal screaming)
2026-03-10 is it fixed?
2026-03-10 Fixed weird footprint sync error that kept popping up on DRC around the mounting holes because of the polygon zone keepout areas. Also found a huge mistake in the schematic, fixed, still needs to be 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
2026-03-10 Whoops, fixed silly ERC errors
2026-03-11 Fixed HW errors
2026-03-11 Fixed OPD connection in schematics and updated tracing and out of date footprints. Ready for final review from andrew
2026-03-11 FIxed OPD connection
2026-03-11 added clearance around HW
2026-03-12 SBAND & HELICAL RF CHANGES
2026-03-12 Another round on the +Z End Card; ready for fab.
    Brushed up RF paths and solder mask, cleaned up UART switches with closer bypass caps, cleaned up a lot of the zones, and lots of little polishing.
2026-03-15 Align SMPM connectors better and add a bit more solder mask keepout
2026-03-24 v1.1 sent to fab
    Updated 3D models of connectors, added missing capacitors, fixed footprints, polished schematic, upgraded to single README file with Makefile.
2026-04-13 ESI v1.0 -Z End Card for fab
    Added makefile and readme, fixed BOM error, moved to better RF zone rules
2026-06-07 Update gitignore for KiCad 10
2026-06-07 ESI -Z End Card updated to v1.1 with extremely minor changes (KiCad 10 update)
    Updated to KiCad 10.0.3, which updated several footprints and re-triggered from ERC
    and DRCs. Those were fixed, and out of an abundance of caution, we upped the version
    number although there's no significant difference with v1.0.
2026-06-07 Importing OreSat0 +Z End Card + Turnstile EAGLE files into a generic +Z end card file for KiCad
    We flew OreSat0 in 2022 with a tri-band turnstile. All files were EAGLE PCB files. This just imports the EAGLE files
    as KiCad files, but they're going ot require a LOT of work to upgrade them to OreSat1 tech.
2026-06-26 Swapped L and L1 Bands
